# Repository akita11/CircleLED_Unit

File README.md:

# CircleLED UNIT

3.5mm角サイズのフルカラーLED(WS2812B-Mini)を36個、円形に配置した直径35mmの円形ディスプレイです。Grove端子から給電・制御することができます。4箇所に固定用の穴(φ2mm)があり（中心から22mmの位置）、またこの穴を含む出っ張りの部分はカットすることもできます。

[M5StackのHEXボード](https://www.switch-science.com/products/6058)や[LEDテープ](https://www.switch-science.com/products/5209/)と同様に使用することができます。（LED数は「36個」に設定してください）

## 使い方（接続方法）

"IN"と表記されたGroveコネクタのいずれかに、マイコン(M5Stack等)からのGroveケーブルを接続します。さらに数珠つなぎで別のLEDテープや本ユニットを接続する場合は、"OUT"と表記されたGroveポートを使用してください。

## Author

Junichi Akita (@akita11) / akita@ifdl.jp

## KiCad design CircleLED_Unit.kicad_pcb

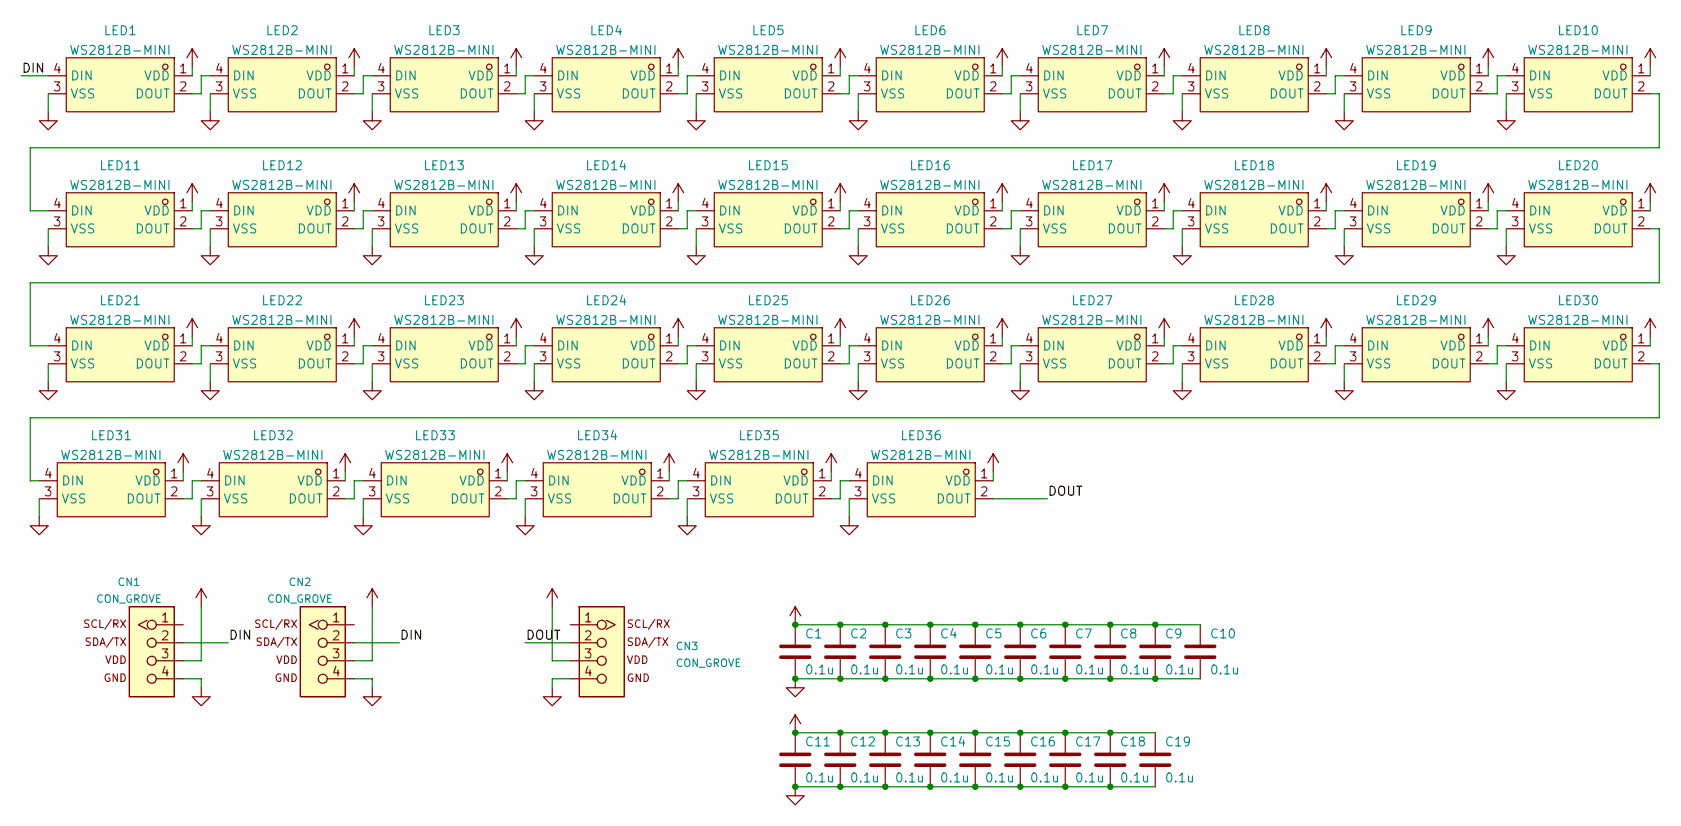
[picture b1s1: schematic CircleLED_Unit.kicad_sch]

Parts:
C1, C2, C3, C4, C5, C6, C7, C8, C9, C10, C11, C12, C13, C14, C15, C16, C17, C18, C19: 0.1u; C_0603_1608Metric
CN1, CN3: CON_GROVE; CON_GROVE_H_SMD
CN2: CON_GROVE; CON_GROVE_V_SMD
LED1, LED2, LED3, LED4, LED5, LED6, LED7, LED8, LED9, LED10, LED11, LED12, LED13, LED14, LED15, LED16, LED17, LED18, LED19, LED20, LED21, LED22, LED23, LED24, LED25, LED26, LED27, LED28, LED29, LED30, LED31, LED32, LED33, LED34, LED35, LED36: WS2812B-MINI; LED-SMD_4P-L3.5-W3.5-TL_WS2812B; LCSC Part C527089

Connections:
/DIN: CN1.2, CN2.2, LED1.4 (DIN)
/DOUT: CN3.2, LED36.2 (DOUT)
GND: C1.2, C2.2, C3.2, C4.2, C5.2, C6.2, C7.2, C8.2, C9.2, C10.2, C11.2, C12.2, C13.2, C14.2, C15.2, C16.2, C17.2, C18.2, C19.2, CN1.4, CN2.4, CN3.4, LED1.3 (VSS), LED2.3 (VSS), LED3.3 (VSS), LED4.3 (VSS), LED5.3 (VSS), LED6.3 (VSS), LED7.3 (VSS), LED8.3 (VSS), LED9.3 (VSS), LED10.3 (VSS), LED11.3 (VSS), LED12.3 (VSS), LED13.3 (VSS), LED14.3 (VSS), LED15.3 (VSS), LED16.3 (VSS), LED17.3 (VSS), LED18.3 (VSS), LED19.3 (VSS), LED20.3 (VSS), LED21.3 (VSS), LED22.3 (VSS), LED23.3 (VSS), LED24.3 (VSS), LED25.3 (VSS), LED26.3 (VSS), LED27.3 (VSS), LED28.3 (VSS), LED29.3 (VSS), LED30.3 (VSS), LED31.3 (VSS), LED32.3 (VSS), LED33.3 (VSS), LED34.3 (VSS), LED35.3 (VSS), LED36.3 (VSS)
unnamed: LED1.2 (DOUT), LED2.4 (DIN)
unnamed: LED2.2 (DOUT), LED3.4 (DIN)
unnamed: LED3.2 (DOUT), LED4.4 (DIN)
unnamed: LED4.2 (DOUT), LED5.4 (DIN)
unnamed: LED5.2 (DOUT), LED6.4 (DIN)
unnamed: LED6.2 (DOUT), LED7.4 (DIN)
unnamed: LED7.2 (DOUT), LED8.4 (DIN)
unnamed: LED8.2 (DOUT), LED9.4 (DIN)
unnamed: LED10.2 (DOUT), LED11.4 (DIN)
unnamed: LED9.2 (DOUT), LED10.4 (DIN)
unnamed: LED11.2 (DOUT), LED12.4 (DIN)
unnamed: LED12.2 (DOUT), LED13.4 (DIN)
unnamed: LED13.2 (DOUT), LED14.4 (DIN)
unnamed: LED14.2 (DOUT), LED15.4 (DIN)
unnamed: LED15.2 (DOUT), LED16.4 (DIN)
unnamed: LED16.2 (DOUT), LED17.4 (DIN)
unnamed: LED17.2 (DOUT), LED18.4 (DIN)
unnamed: LED18.2 (DOUT), LED19.4 (DIN)
unnamed: LED19.2 (DOUT), LED20.4 (DIN)
unnamed: LED20.2 (DOUT), LED21.4 (DIN)
unnamed: LED21.2 (DOUT), LED22.4 (DIN)
unnamed: LED22.2 (DOUT), LED23.4 (DIN)
unnamed: LED23.2 (DOUT), LED24.4 (DIN)
unnamed: LED24.2 (DOUT), LED25.4 (DIN)
unnamed: LED25.2 (DOUT), LED26.4 (DIN)
unnamed: LED26.2 (DOUT), LED27.4 (DIN)
unnamed: LED27.2 (DOUT), LED28.4 (DIN)
unnamed: LED28.2 (DOUT), LED29.4 (DIN)
unnamed: LED29.2 (DOUT), LED30.4 (DIN)
unnamed: LED30.2 (DOUT), LED31.4 (DIN)
unnamed: LED31.2 (DOUT), LED32.4 (DIN)
unnamed: LED32.2 (DOUT), LED33.4 (DIN)
unnamed: LED33.2 (DOUT), LED34.4 (DIN)
unnamed: LED34.2 (DOUT), LED35.4 (DIN)
unnamed: LED35.2 (DOUT), LED36.4 (DIN)
VDD: C1.1, C2.1, C3.1, C4.1, C5.1, C6.1, C7.1, C8.1, C9.1, C10.1, C11.1, C12.1, C13.1, C14.1, C15.1, C16.1, C17.1, C18.1, C19.1, CN1.3, CN2.3, CN3.3, LED1.1 (VDD), LED2.1 (VDD), LED3.1 (VDD), LED4.1 (VDD), LED5.1 (VDD), LED6.1 (VDD), LED7.1 (VDD), LED8.1 (VDD), LED9.1 (VDD), LED10.1 (VDD), LED11.1 (VDD), LED12.1 (VDD), LED13.1 (VDD), LED14.1 (VDD), LED15.1 (VDD), LED16.1 (VDD), LED17.1 (VDD), LED18.1 (VDD), LED19.1 (VDD), LED20.1 (VDD), LED21.1 (VDD), LED22.1 (VDD), LED23.1 (VDD), LED24.1 (VDD), LED25.1 (VDD), LED26.1 (VDD), LED27.1 (VDD), LED28.1 (VDD), LED29.1 (VDD), LED30.1 (VDD), LED31.1 (VDD), LED32.1 (VDD), LED33.1 (VDD), LED34.1 (VDD), LED35.1 (VDD), LED36.1 (VDD)

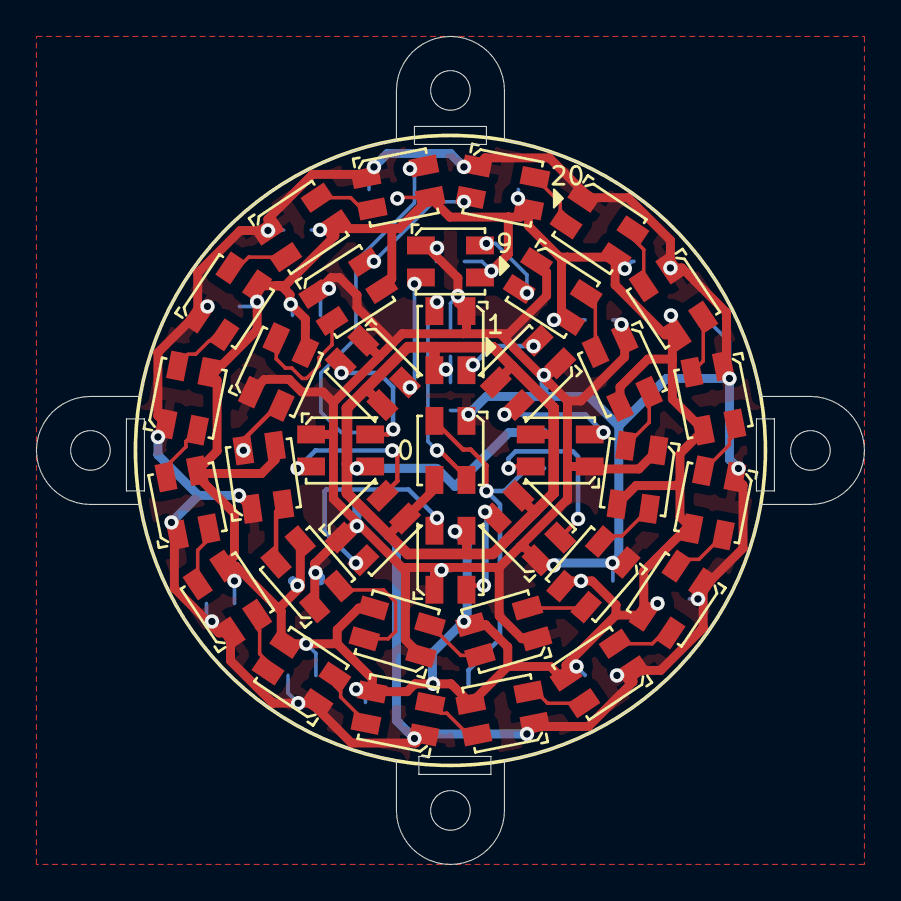
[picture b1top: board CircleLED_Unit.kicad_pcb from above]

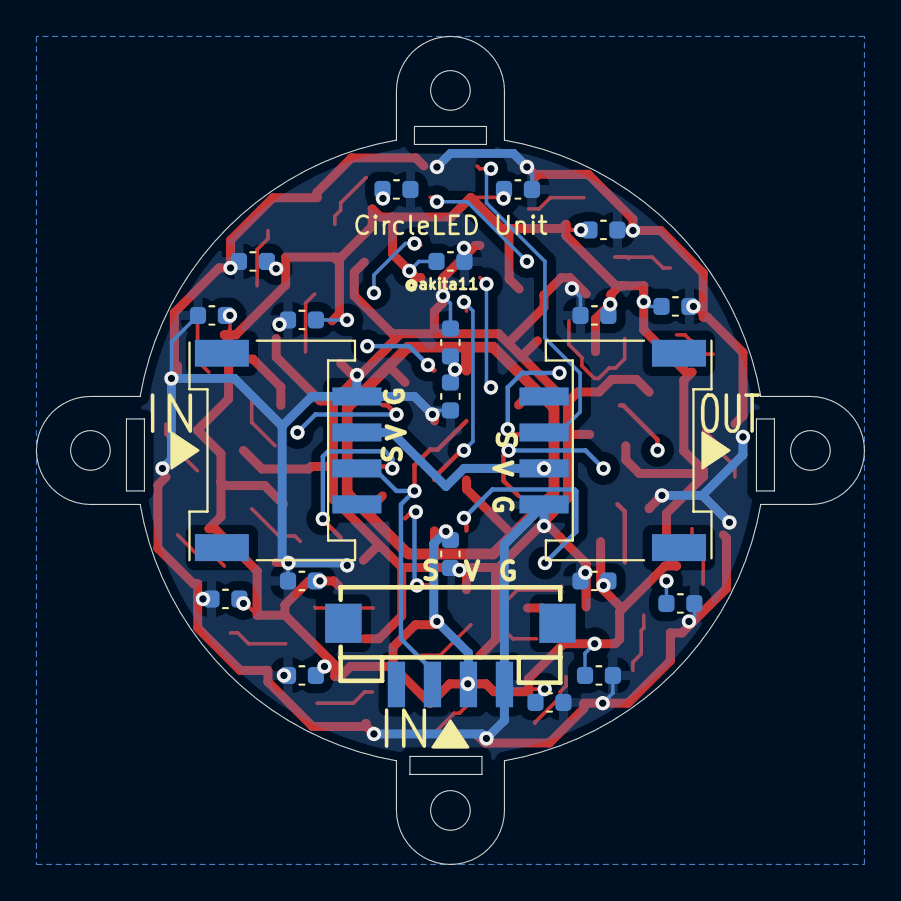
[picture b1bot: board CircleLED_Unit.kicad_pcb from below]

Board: 2 copper layers, 46.0 x 46.0 mm, 58 parts (22 on the bottom side), 39 nets.

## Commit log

2025-01-30 typo fix
